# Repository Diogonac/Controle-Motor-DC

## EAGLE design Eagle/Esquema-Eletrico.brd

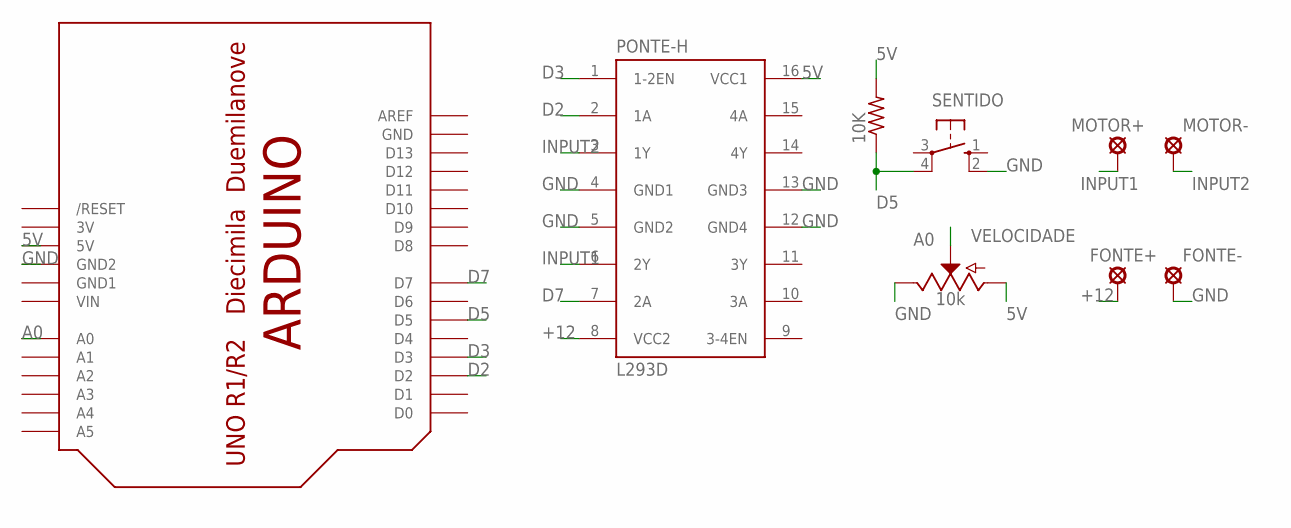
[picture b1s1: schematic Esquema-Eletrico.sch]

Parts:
10K: R-US_0207/12; 0207/12
FONTE+: LSP10
FONTE-: LSP10
MOTOR+: LSP10
MOTOR-: LSP10
PONTE-H: L293D; DIL16
SENTIDO: 10-XX; B3F-10XX
U$1: ARDUINOUNO; ARDUINO
VELOCIDADE: 10k; POT-PTH-ALPS

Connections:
3V: U$1.3V
5V: 10K.2, PONTE-H.16 (VCC1), U$1.5V, VELOCIDADE.P$3 (A)
+12: FONTE+.MP, PONTE-H.8 (VCC2)
A0: U$1.A0, VELOCIDADE.P$2 (S)
D2: PONTE-H.2 (1A), U$1.D2
D3: PONTE-H.1 (1-2EN), U$1.D3
D5: 10K.1, SENTIDO.4 (P1), U$1.D5
D7: PONTE-H.7 (2A), U$1.D7
GND: FONTE-.MP, PONTE-H.4 (GND1), PONTE-H.5 (GND2), PONTE-H.12 (GND4), PONTE-H.13 (GND3), SENTIDO.2 (S1), U$1.GND, U$1.GND2, VELOCIDADE.P$1 (E)
GND1: U$1.GND1
INPUT1: MOTOR+.MP, PONTE-H.6 (2Y)
INPUT2: MOTOR-.MP, PONTE-H.3 (1Y)
VIN: U$1.VIN

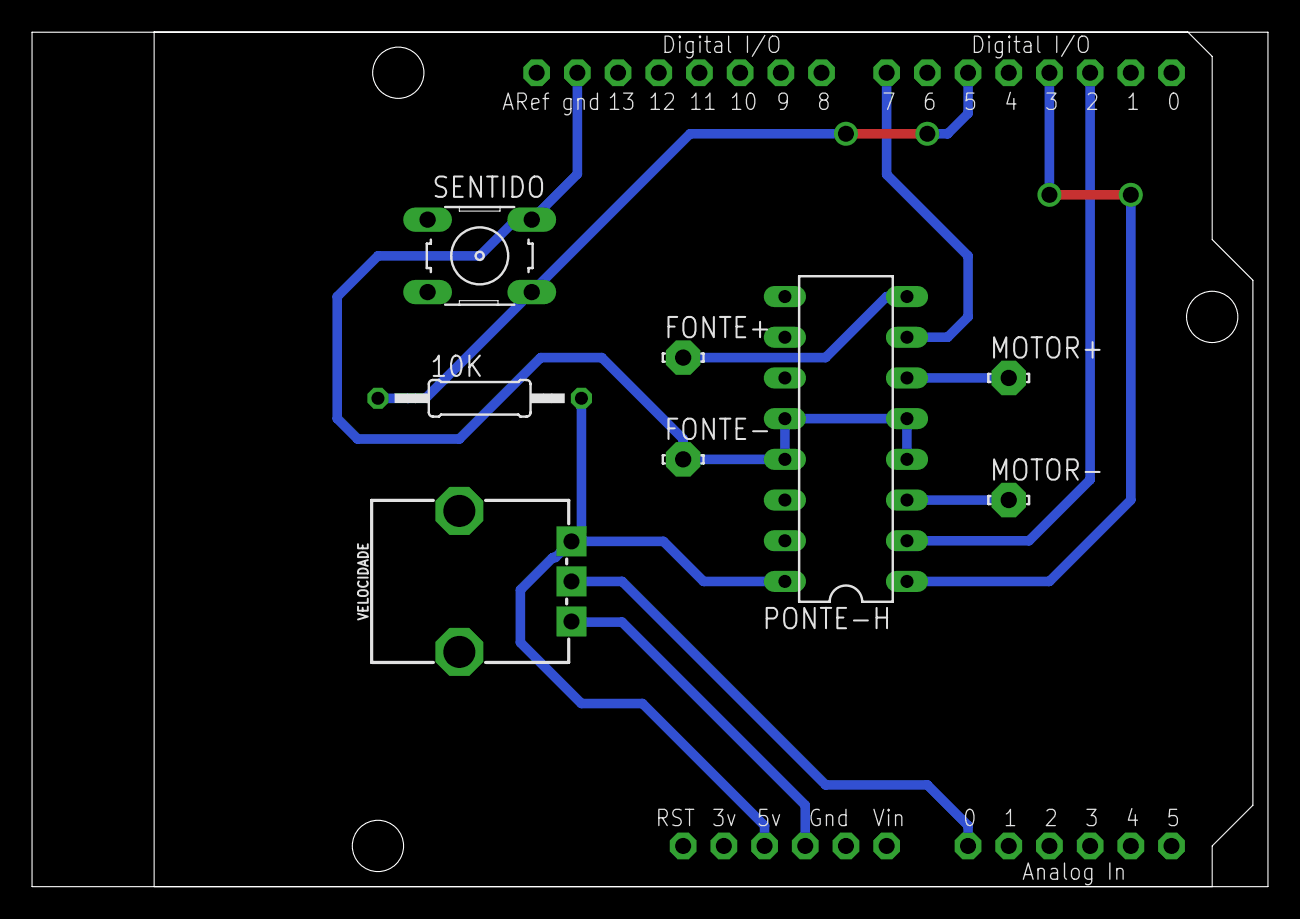
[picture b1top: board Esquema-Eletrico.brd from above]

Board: 2 copper layers, 77.1 x 53.3 mm, 9 parts (0 on the bottom side), 10 nets.

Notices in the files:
parts and their libraries:
SparkFun-Resistors: Licensing: Creative Commons ShareAlike 4.0 International - https://creativecommons.org/licenses/by-sa/4.0
